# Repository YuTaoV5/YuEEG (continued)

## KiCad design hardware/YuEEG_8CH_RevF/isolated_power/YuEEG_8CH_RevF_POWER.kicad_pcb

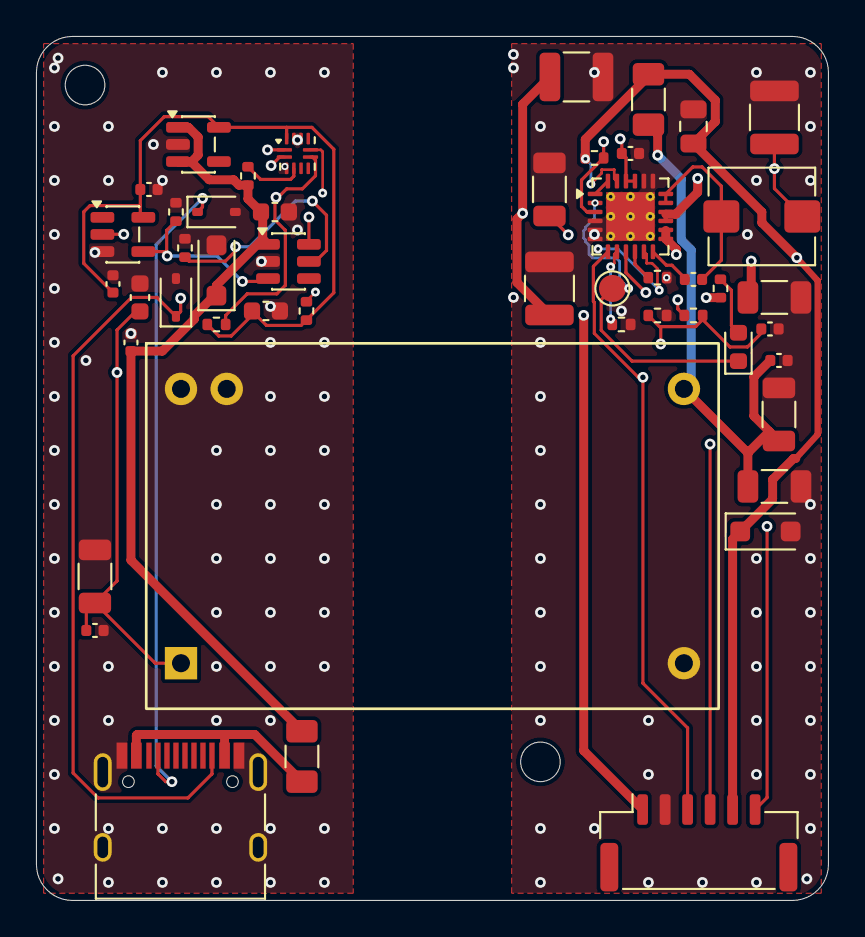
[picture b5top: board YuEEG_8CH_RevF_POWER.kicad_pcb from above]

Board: 4 copper layers, 44.0 x 48.0 mm, 50 parts (0 on the bottom side), 29 nets.

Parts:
C601: 4.7u 16V X7R; C_0805_2012Metric
C602, C605, C606: 47u 16V X7R; C_1210_3225Metric
C603, C609, C706, C707, C709, C1202, C1204: 100n 16V; C_0402_1005Metric
C604: 22u 16V X7R; C_1206_3216Metric
C607: 22u 25V X7R; C_1206_3216Metric
C608: 47n 25V X7R; C_0402_1005Metric
C704: 1u 16V; C_0603_1608Metric
C705: 1u 10V; C_0603_1608Metric
C708: 4.7u 16V; C_0603_1608Metric
C710, C1201, C1203: 10u 25V X7R; C_1206_3216Metric
D601, D701: SMF5.0A; D_SOD-123F
D902, D903: PESD5V0S1BA; D_SOD-323
F602: 1A hold PTC; Fuse_1206_3216Metric
F701: 1.5A hold PTC; Fuse_1206_3216Metric
H1205, H1206: M2 INSULATED MOUNT; MountingHole_2.2mm_M2
J901: USB-C CHARGE / POWER - NO DATA; USB_C_Receptacle_HRO_TYPE-C-31-M-12
J1204: TO MAIN J1202 / GH6; JST_GH_SM06B-GHS-TB_1x06-1MP_P1.25mm_Horizontal
L601: 1uH SRP5030T-1R0M / Isat11A; L_Bourns_SRP5030T
LED601: CHARGING; LED_0603_1608Metric
R601, R602: 10k 1%; R_0402_1005Metric
R603: 1.50k 1%; R_0402_1005Metric
R604: 1.14k 1%; R_0402_1005Metric
R605: 9.31k 0.1%; R_0402_1005Metric
R606: 365k 0.1%; R_0402_1005Metric
R609: 2.2k; R_0402_1005Metric
R705: 887k 1%; R_0402_1005Metric
R706: 23.7k 1%; R_0402_1005Metric
R707: 100k; R_0402_1005Metric
R1205: 1M CE DEFAULT OFF; R_0402_1005Metric
TP606: CHG_STAT; TestPoint_Pad_D1.5mm
U601: BQ25886RGER; Texas_RGE0024H_VQFN-24-1EP_4x4mm_P0.5mm_EP2.7x2.7mm_Thermal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
U702: TLV75533PDBVR HOST ONLY; SOT-23-5
U703: TUSB320LAIRWBR / UFP GPIO; Texas_X2QFN-12_1.6x1.6mm_P0.4mm
U704: SN74LVC1G04DBVR; SOT-23-5
U705: TPS2553DBVR; SOT-23-6
U706: THM 6-0511 / STANDARD PINOUT; THM6_Standard

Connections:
CC_HIGH_N: R601.2, U703.7, U704.2
CC_MODE2: R602.2, U703.8
CC_VBUS_DET: R705.2, U703.4
CHARGE_CC1: D902.1, J901.A5, U703.1
CHARGE_CC2: D903.1, J901.B5, U703.2
CHARGE_HOST_3V3: C705.1, C706.1, C707.1, R601.1, R602.1, U702.5, U703.12, U704.5
CHARGE_HOST_5V: C704.1, C709.1, D701.1, F701.2, R705.1, U702.1, U702.3, U705.1
CHARGE_HOST_DCDC_IN: C708.1, C1201.1, C1202.1, U705.6, U706.1
CHARGE_HOST_GND: C704.2, C705.2, C706.2, C707.2, C708.2, C709.2, C1201.2, C1202.2, D701.2, D902.2, D903.2, J901.A1, J901.A12, J901.B1, J901.B12, J901.S1, R706.2, R707.2, U702.2, U703.3, U703.10, U703.11, U704.3, U705.2, U706.23, U706.24
CHARGE_HOST_ILIM: R706.1, U705.5
CHARGE_HOST_POWER_EN: R707.1, U704.4, U705.3
CHARGE_HOST_RAW: F701.1, J901.A4, J901.A9, J901.B4, J901.B9
CHG_BOOT: C608.1, U601.12
CHG_CE: J1204.4, R1205.2, U601.3
CHG_DETECT: U601.1, U601.24
CHG_ILIM: R603.1, U601.8
CHG_ISET: R604.1, U601.10
CHG_PG: J1204.6, U601.9
CHG_PMID: C602.1, C603.1, L601.1, U601.21, U601.22
CHG_REGN: C604.1, R605.1, U601.11
CHG_STAT: LED601.1, TP606.1, U601.2
CHG_SW: C608.2, L601.2, U601.17, U601.18
CHG_SYS: C605.1, C606.1, U601.15, U601.16
CHG_TS: C609.1, J1204.3, R605.2, R606.1, U601.7
GND: C601.2, C602.2, C603.2, C604.2, C605.2, C606.2, C607.2, C609.2, C710.2, C1203.2, C1204.2, D601.2, J1204.2, R603.2, R604.2, R606.2, U601.4, U601.5, U601.6, U601.19, U601.20, U601.25, U706.12
LED_CHG_A: LED601.2, R609.2
PACK_POS: C607.1, J1204.1, U601.13, U601.14
USB5: C601.1, D601.1, F602.2, J1204.5, R609.1, R1205.1, U601.23
USB_RAW: C710.1, C1203.1, C1204.1, F602.1, U706.13

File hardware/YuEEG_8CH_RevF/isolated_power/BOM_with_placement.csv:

Reference,Value,Footprint,Side,X_mm_from_left,Y_mm_from_top,Rotation_deg
C1201,10u 25V X7R,Capacitor_SMD:C_1206_3216Metric,TOP,3.25,30.0,90.0
C1202,100n 16V,Capacitor_SMD:C_0402_1005Metric,TOP,3.25,33.0,0.0
C1203,10u 25V X7R,Capacitor_SMD:C_1206_3216Metric,TOP,41.25,21.0,90.0
C1204,100n 16V,Capacitor_SMD:C_0402_1005Metric,TOP,41.25,18.0,0.0
C601,4.7u 16V X7R,Capacitor_SMD:C_0805_2012Metric,TOP,36.5,5.0,90.0
C602,47u 16V X7R,Capacitor_SMD:C_1210_3225Metric,TOP,41.0,4.5,90.0
C603,100n 16V,Capacitor_SMD:C_0402_1005Metric,TOP,33.0,6.5,0.0
C604,22u 16V X7R,Capacitor_SMD:C_1206_3216Metric,TOP,28.5,8.5,90.0
C605,47u 16V X7R,Capacitor_SMD:C_1210_3225Metric,TOP,28.5,14.0,90.0
C606,47u 16V X7R,Capacitor_SMD:C_1210_3225Metric,TOP,30.0,2.25,0.0
C607,22u 25V X7R,Capacitor_SMD:C_1206_3216Metric,TOP,41.0,14.5,0.0
C608,47n 25V X7R,Capacitor_SMD:C_0402_1005Metric,TOP,36.5,13.5,0.0
C609,100n 16V,Capacitor_SMD:C_0402_1005Metric,TOP,40.75,16.25,0.0
C704,1u 16V,Capacitor_SMD:C_0603_1608Metric,TOP,13.25,9.75,0.0
C705,1u 10V,Capacitor_SMD:C_0603_1608Metric,TOP,12.75,15.25,0.0
C706,100n 16V,Capacitor_SMD:C_0402_1005Metric,TOP,6.25,8.5,0.0
C707,100n 16V,Capacitor_SMD:C_0402_1005Metric,TOP,4.25,13.75,90.0
C708,4.7u 16V,Capacitor_SMD:C_0603_1608Metric,TOP,5.75,14.5,90.0
C709,100n 16V,Capacitor_SMD:C_0402_1005Metric,TOP,5.25,17.0,90.0
C710,10u 25V X7R,Capacitor_SMD:C_1206_3216Metric,TOP,41.0,25.0,0.0
D601,SMF5.0A,Diode_SMD:D_SOD-123F,TOP,40.5,27.5,0.0
D701,SMF5.0A,Diode_SMD:D_SOD-123F,TOP,10.0,13.0,90.0
D902,PESD5V0S1BA,Diode_SMD:D_SOD-323,TOP,10.0,9.75,0.0
D903,PESD5V0S1BA,Diode_SMD:D_SOD-323,TOP,7.75,14.5,90.0
F602,1A hold PTC,Fuse:Fuse_1206_3216Metric,TOP,34.0,3.5,90.0
F701,1.5A hold PTC,Fuse:Fuse_1206_3216Metric,TOP,14.75,40.0,90.0
H1205,M2 INSULATED MOUNT,MountingHole:MountingHole_2.2mm_M2,TOP,2.7,2.7,0.0
H1206,M2 INSULATED MOUNT,MountingHole:MountingHole_2.2mm_M2,TOP,28.0,40.3,0.0
J1204,TO MAIN J1202 / GH6,Connector_JST:JST_GH_SM06B-GHS-TB_1x06-1MP_P1.25mm_Horizontal,TOP,36.8,44.8,0.0
J901,USB-C CHARGE / POWER - NO DATA,Connector_USB:USB_C_Receptacle_HRO_TYPE-C-31-M-12,TOP,8.0,44.0,0.0
L601,1uH SRP5030T-1R0M / Isat11A,Inductor_SMD:L_Bourns_SRP5030T,TOP,40.3,10.0,180.0
LED601,CHARGING,LED_SMD:LED_0603_1608Metric,TOP,39.0,17.25,90.0
R1205,1M CE DEFAULT OFF,Resistor_SMD:R_0402_1005Metric,TOP,31.0,6.75,0.0
R601,10k 1%,Resistor_SMD:R_0402_1005Metric,TOP,10.0,16.0,0.0
R602,10k 1%,Resistor_SMD:R_0402_1005Metric,TOP,15.0,15.25,90.0
R603,1.50k 1%,Resistor_SMD:R_0402_1005Metric,TOP,32.5,16.0,0.0
R604,1.14k 1%,Resistor_SMD:R_0402_1005Metric,TOP,34.5,13.4,0.0
R605,9.31k 0.1%,Resistor_SMD:R_0402_1005Metric,TOP,36.5,15.5,0.0
R606,365k 0.1%,Resistor_SMD:R_0402_1005Metric,TOP,34.5,15.5,0.0
R609,2.2k,Resistor_SMD:R_0402_1005Metric,TOP,38.0,14.0,90.0
R705,887k 1%,Resistor_SMD:R_0402_1005Metric,TOP,11.75,7.75,90.0
R706,23.7k 1%,Resistor_SMD:R_0402_1005Metric,TOP,8.25,11.75,90.0
R707,100k,Resistor_SMD:R_0402_1005Metric,TOP,7.75,9.75,90.0
TP606,CHG_STAT,TestPoint:TestPoint_Pad_D1.5mm,TOP,32.0,14.0,0.0
U601,BQ25886RGER,Package_DFN_QFN:Texas_RGE0024H_VQFN-24-1EP_4x4mm_P0.5mm_EP2.7x2.7mm_ThermalVias,TOP,33.0,10.0,0.0
U702,TLV75533PDBVR HOST ONLY,Package_TO_SOT_SMD:SOT-23-5,TOP,9.0,6.0,0.0
U703,TUSB320LAIRWBR / UFP GPIO,Package_DFN_QFN:Texas_X2QFN-12_1.6x1.6mm_P0.4mm,TOP,14.5,6.5,0.0
U704,SN74LVC1G04DBVR,Package_TO_SOT_SMD:SOT-23-5,TOP,4.8,11.0,0.0
U705,TPS2553DBVR,Package_TO_SOT_SMD:SOT-23-6,TOP,14.0,12.5,0.0
U706,THM 6-0511 / STANDARD PINOUT,YuEEG:THM6_Standard,TOP,22.0,27.2,0.0

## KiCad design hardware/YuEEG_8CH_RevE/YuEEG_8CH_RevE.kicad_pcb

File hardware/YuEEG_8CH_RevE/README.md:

# YuEEG Rev E 工程评审版

94 × 122 mm、四层、378 个元件、15 页原理图。以 `YuEEG_8CH_RevE.kicad_pro` 打开 KiCad 9 工程。

- 双 Type-C 同边：DATA/FLASH 为隔离原生 USB，CHARGE/POWER 为独立充电/供电；VBUS 不并联。
- ESP32-S3-WROOM-1-N16R8；USB CDC 与 Wi-Fi UDP 并行；SDMMC microSD 备份。
- DWO DO0200PFS12 RM67162 1.91 英寸 AMOLED，专用 2.8/1.8 V 电源及电平转换；需要确认供应商版本和配套排线。
- 0.53 mm Panasonic EVPBB2A9B000 超薄贴片 RESET/BOOT/REC；电解电容和按钮均在正面。
- CH1–8、REF、BIAS 同列；移除外置模拟前端扩展接口，恢复直接对称 P/N 输入路径。
- 圆角板框、圆角丝印分区、分组状态灯；黑色阻焊/白字/ENIG 外观。

## 文件入口

- [原理图 PDF](YuEEG_8CH_RevE.pdf)
- [设计分析与一手资料](REV_E_REVIEW.md)
- [静态检查结果](review/PCB_validation.json)
- [加工/装配要求](fabrication_review/ASSEMBLY_NOTES.md)
- [模块、排线和支撑件清单](ASSEMBLY_EXTRAS.csv)
- [固件操作说明](firmware/ads1299_driver/README.md)
- [正面预览](review/PCB_3D_top.png) · [背面预览](review/PCB_3D_bottom.png)

原理图、PCB、加工文件、引脚复核及固件快照由 CHECKSUMS.json 绑定。过孔填孔/铜封帽、模块与外壳的实际配合、屏幕初始化、SD 卡延迟、并行传输及模拟噪声需要首板验证。3D 中屏幕图案仅为布局示意，模型不替代供应商机械图。工程评审通过不等于人体使用放行或医疗认证。

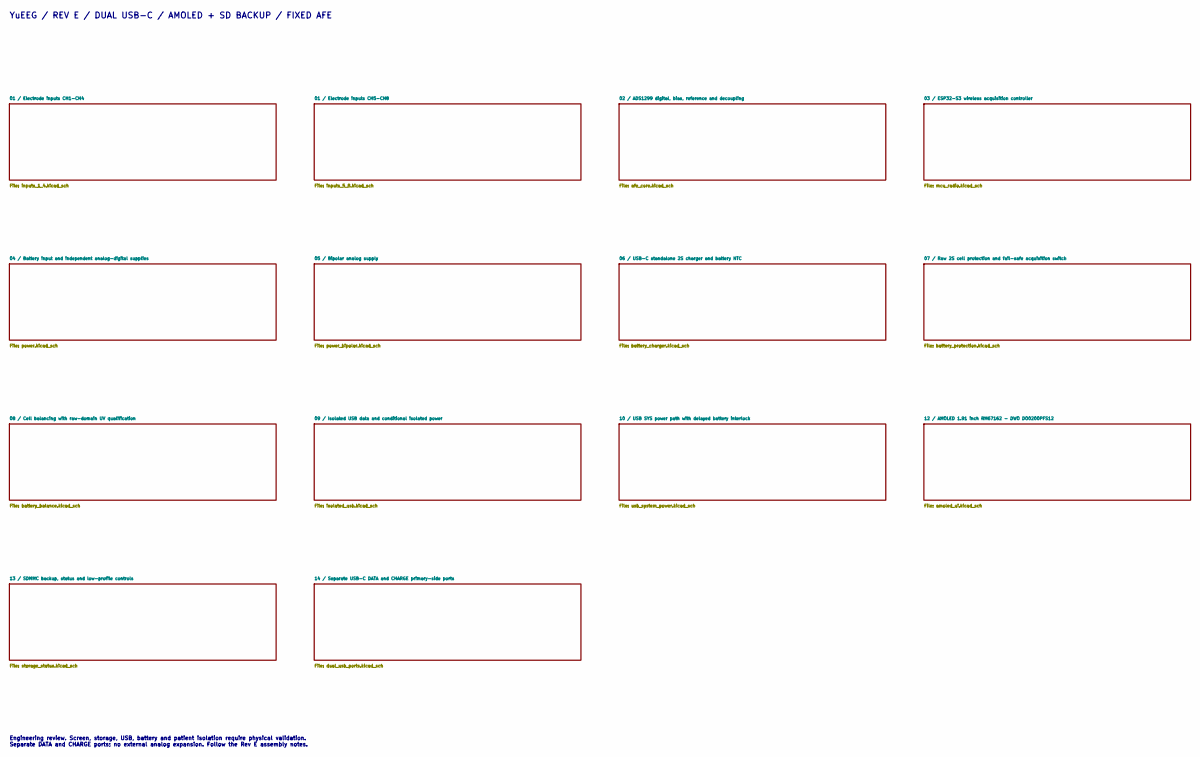
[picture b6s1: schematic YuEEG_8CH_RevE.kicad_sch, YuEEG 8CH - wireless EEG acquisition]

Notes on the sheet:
YuEEG / REV E / DUAL USB-C / AMOLED + SD BACKUP / FIXED AFE
Engineering review. Screen, storage, USB, battery and patient isolation require physical validation. Separate DATA and CHARGE ports; no external analog expansion. Follow the Rev E assembly notes.

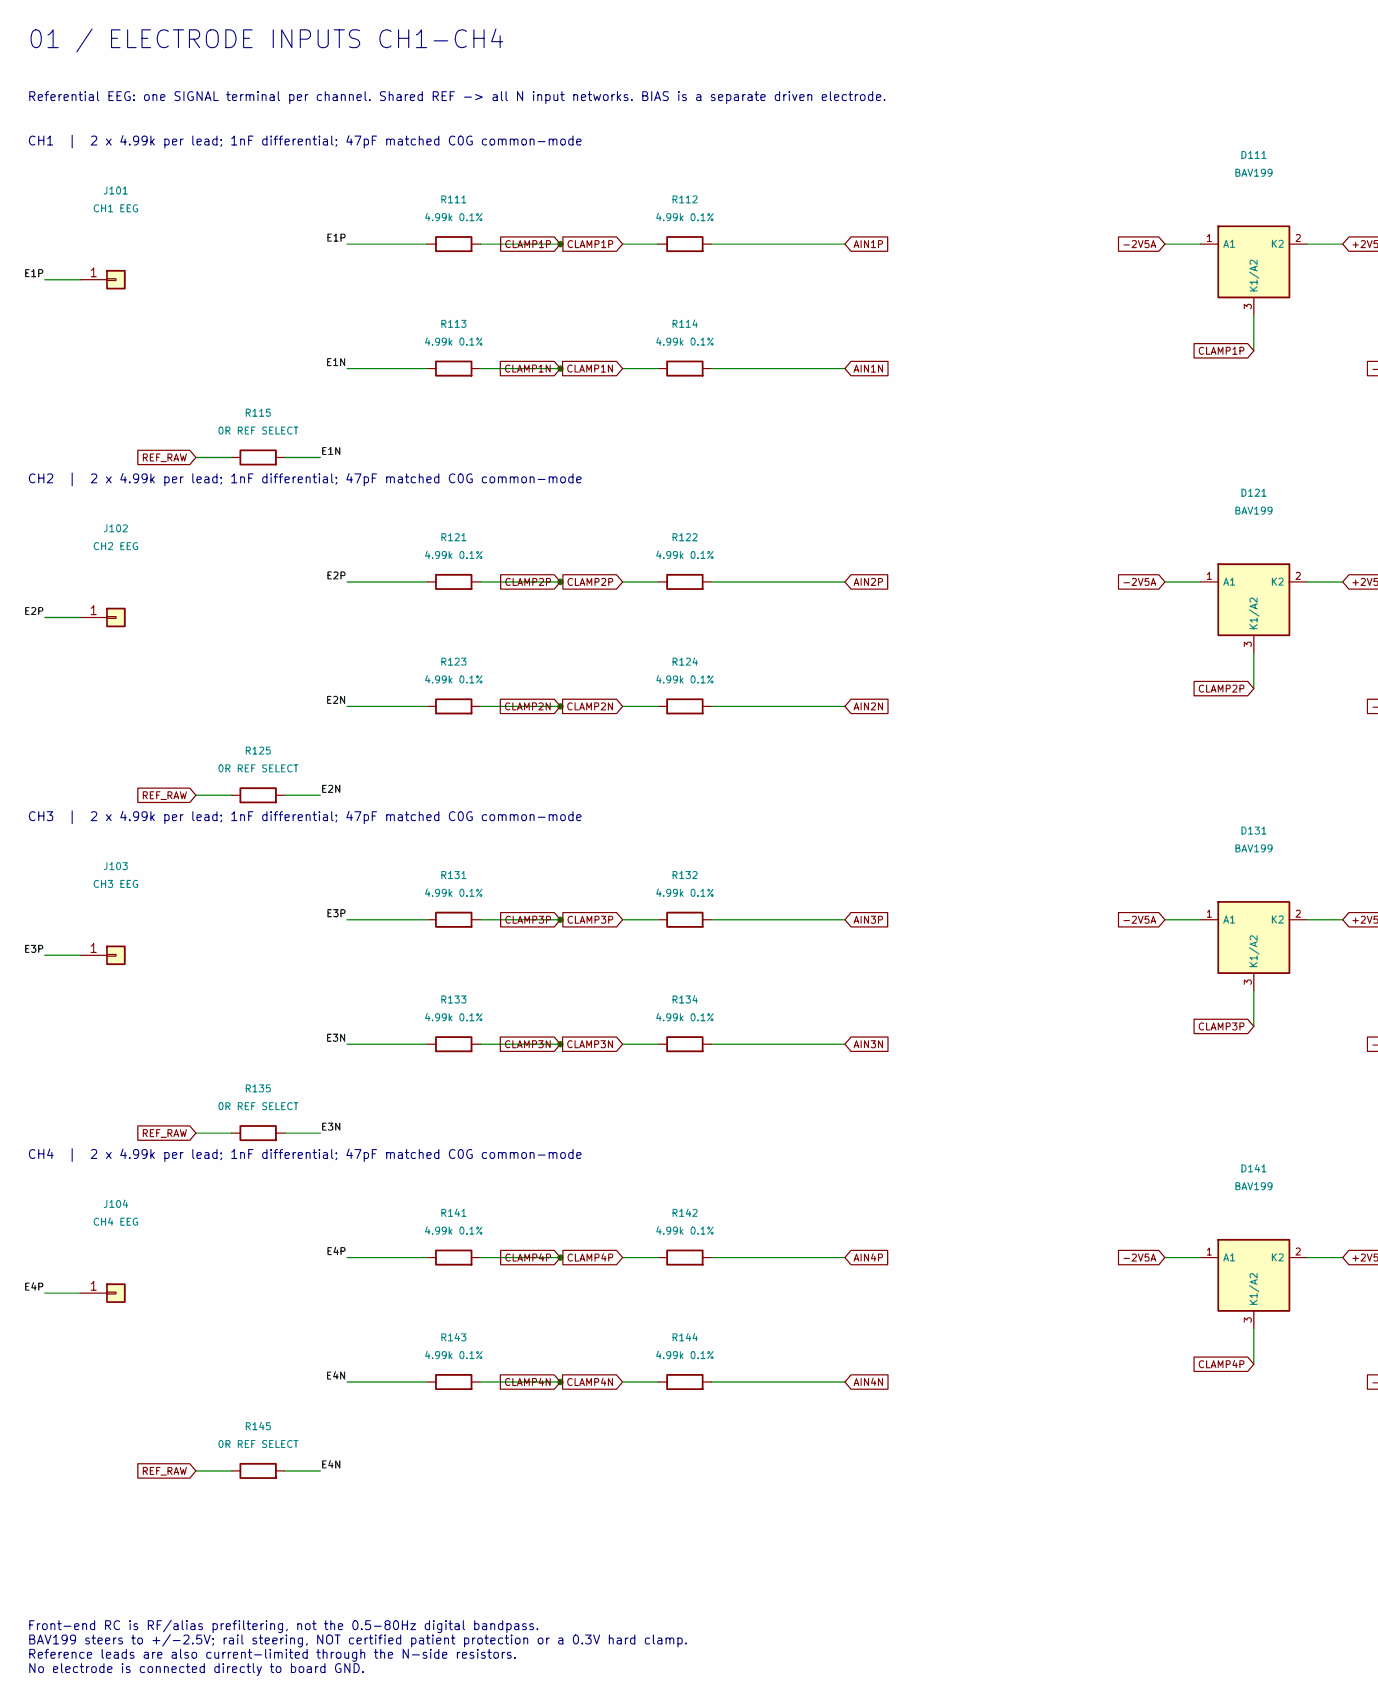
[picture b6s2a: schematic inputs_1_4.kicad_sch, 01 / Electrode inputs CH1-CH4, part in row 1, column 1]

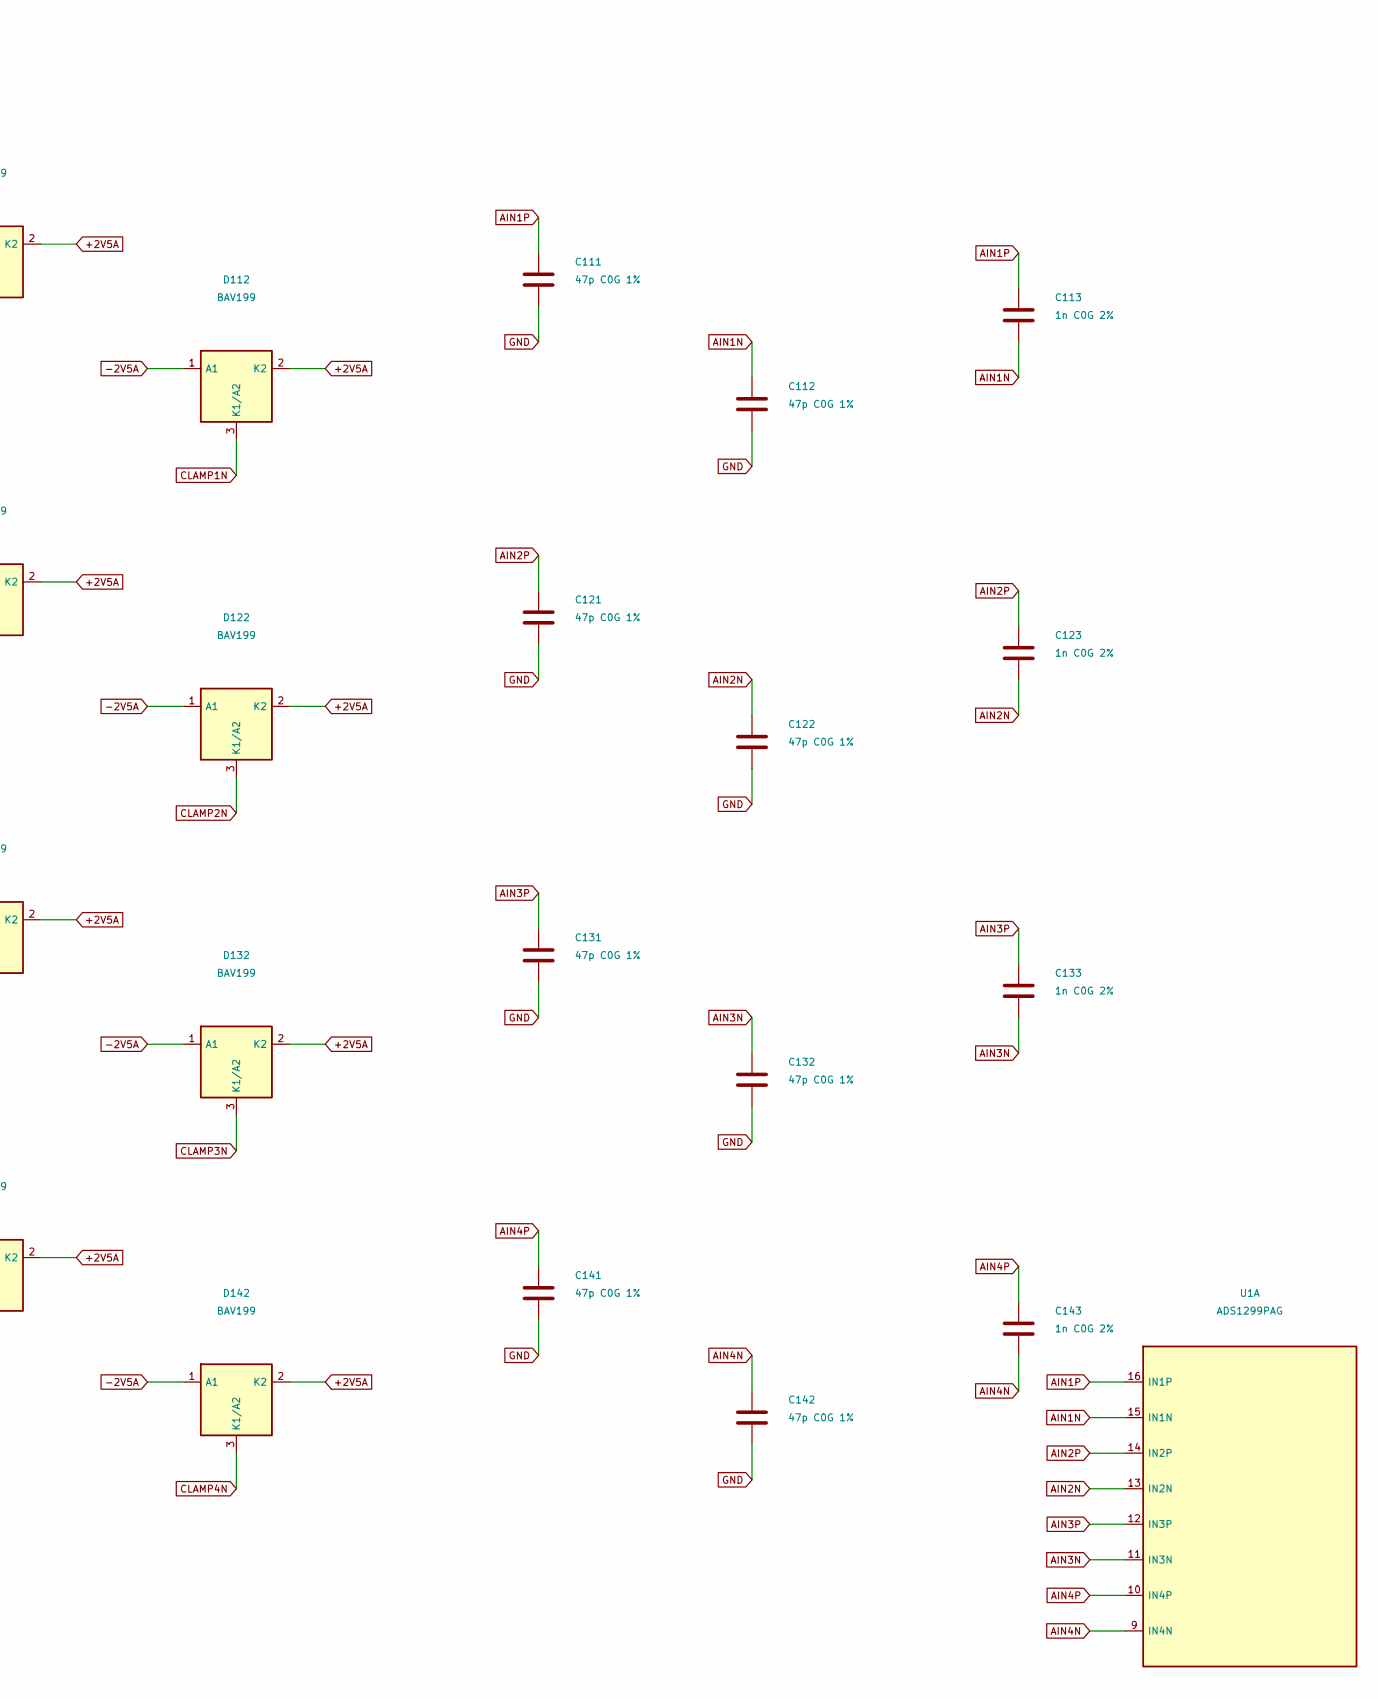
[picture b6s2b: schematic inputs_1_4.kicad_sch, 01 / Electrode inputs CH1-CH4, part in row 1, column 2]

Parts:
C111, C112, C121, C122, C131, C132, C141, C142: 47p C0G 1%; C_0603_1608Metric
C113, C123, C133, C143: 1n C0G 2%; C_0603_1608Metric
D111, D112, D121, D122, D131, D132, D141, D142: BAV199; SOT-23
J101: CH1 EEG; PinHeader_1x01_P2.54mm_Vertical
J102: CH2 EEG; PinHeader_1x01_P2.54mm_Vertical
J103: CH3 EEG; PinHeader_1x01_P2.54mm_Vertical
J104: CH4 EEG; PinHeader_1x01_P2.54mm_Vertical
R111, R112, R113, R114, R121, R122, R123, R124, R131, R132, R133, R134, R141, R142, R143, R144: 4.99k 0.1%; R_0603_1608Metric
R115, R125, R135, R145: 0R REF SELECT; R_0603_1608Metric
U1: ADS1299PAG; TQFP-64_10x10mm_P0.5mm

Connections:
+2V5A: D111.2 (K2), D112.2 (K2), D121.2 (K2), D122.2 (K2), D131.2 (K2), D132.2 (K2), D141.2 (K2), D142.2 (K2); also elsewhere on the board
-2V5A: D111.1 (A1), D112.1 (A1), D121.1 (A1), D122.1 (A1), D131.1 (A1), D132.1 (A1), D141.1 (A1), D142.1 (A1); also elsewhere on the board
/01 / Electrode inputs CH1-CH4/E1N: R113.1, R115.2
/01 / Electrode inputs CH1-CH4/E1P: J101.1, R111.1
/01 / Electrode inputs CH1-CH4/E2N: R123.1, R125.2
/01 / Electrode inputs CH1-CH4/E2P: J102.1, R121.1
/01 / Electrode inputs CH1-CH4/E3N: R133.1, R135.2
/01 / Electrode inputs CH1-CH4/E3P: J103.1, R131.1
/01 / Electrode inputs CH1-CH4/E4N: R143.1, R145.2
/01 / Electrode inputs CH1-CH4/E4P: J104.1, R141.1
AIN1N: C112.1, C113.2, R114.2, U1.15 (IN1N)
AIN1P: C111.1, C113.1, R112.2, U1.16 (IN1P)
AIN2N: C122.1, C123.2, R124.2, U1.13 (IN2N)
AIN2P: C121.1, C123.1, R122.2, U1.14 (IN2P)
AIN3N: C132.1, C133.2, R134.2, U1.11 (IN3N)
AIN3P: C131.1, C133.1, R132.2, U1.12 (IN3P)
AIN4N: C142.1, C143.2, R144.2, U1.9 (IN4N)
AIN4P: C141.1, C143.1, R142.2, U1.10 (IN4P)
CLAMP1N: D112.3 (K1/A2), R113.2, R114.1
CLAMP1P: D111.3 (K1/A2), R111.2, R112.1
CLAMP2N: D122.3 (K1/A2), R123.2, R124.1
CLAMP2P: D121.3 (K1/A2), R121.2, R122.1
CLAMP3N: D132.3 (K1/A2), R133.2, R134.1
CLAMP3P: D131.3 (K1/A2), R131.2, R132.1
CLAMP4N: D142.3 (K1/A2), R143.2, R144.1
CLAMP4P: D141.3 (K1/A2), R141.2, R142.1
GND: C111.2, C112.2, C121.2, C122.2, C131.2, C132.2, C141.2, C142.2; also elsewhere on the board
REF_RAW: R115.1, R125.1, R135.1, R145.1; also elsewhere on the board

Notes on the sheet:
01 / ELECTRODE INPUTS CH1-CH4
Referential EEG: one SIGNAL terminal per channel. Shared REF -> all N input networks. BIAS is a separate driven electrode.
CH1 | 2 x 4.99k per lead; 1nF differential; 47pF matched C0G common-mode
CH2 | 2 x 4.99k per lead; 1nF differential; 47pF matched C0G common-mode
CH3 | 2 x 4.99k per lead; 1nF differential; 47pF matched C0G common-mode
CH4 | 2 x 4.99k per lead; 1nF differential; 47pF matched C0G common-mode
Front-end RC is RF/alias prefiltering, not the 0.5-80Hz digital bandpass. BAV199 steers to +/-2.5V; rail steering, NOT certified patient protection or a 0.3V hard clamp. Reference leads are also current-limited through the N-side resistors. No electrode is connected directly to board GND.

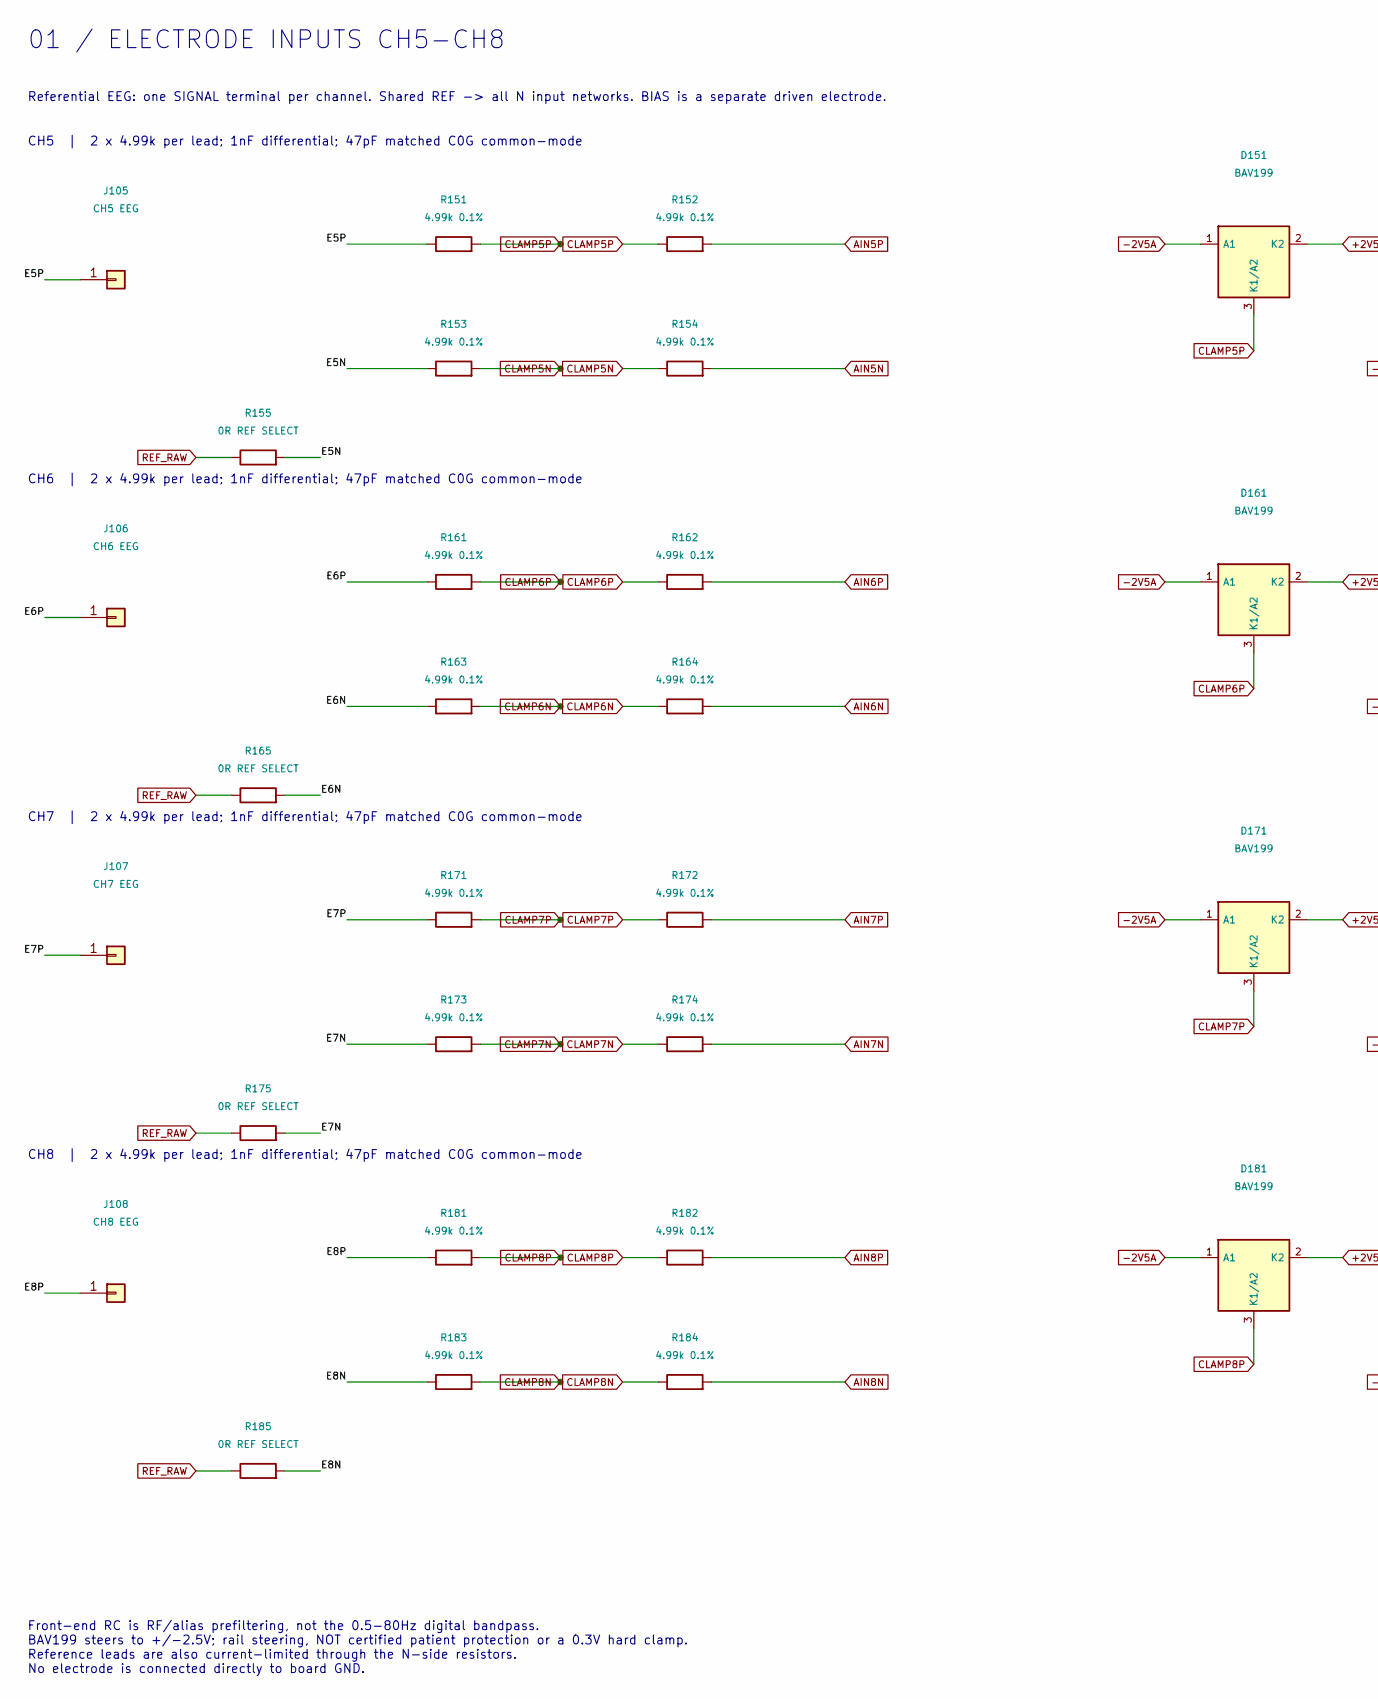
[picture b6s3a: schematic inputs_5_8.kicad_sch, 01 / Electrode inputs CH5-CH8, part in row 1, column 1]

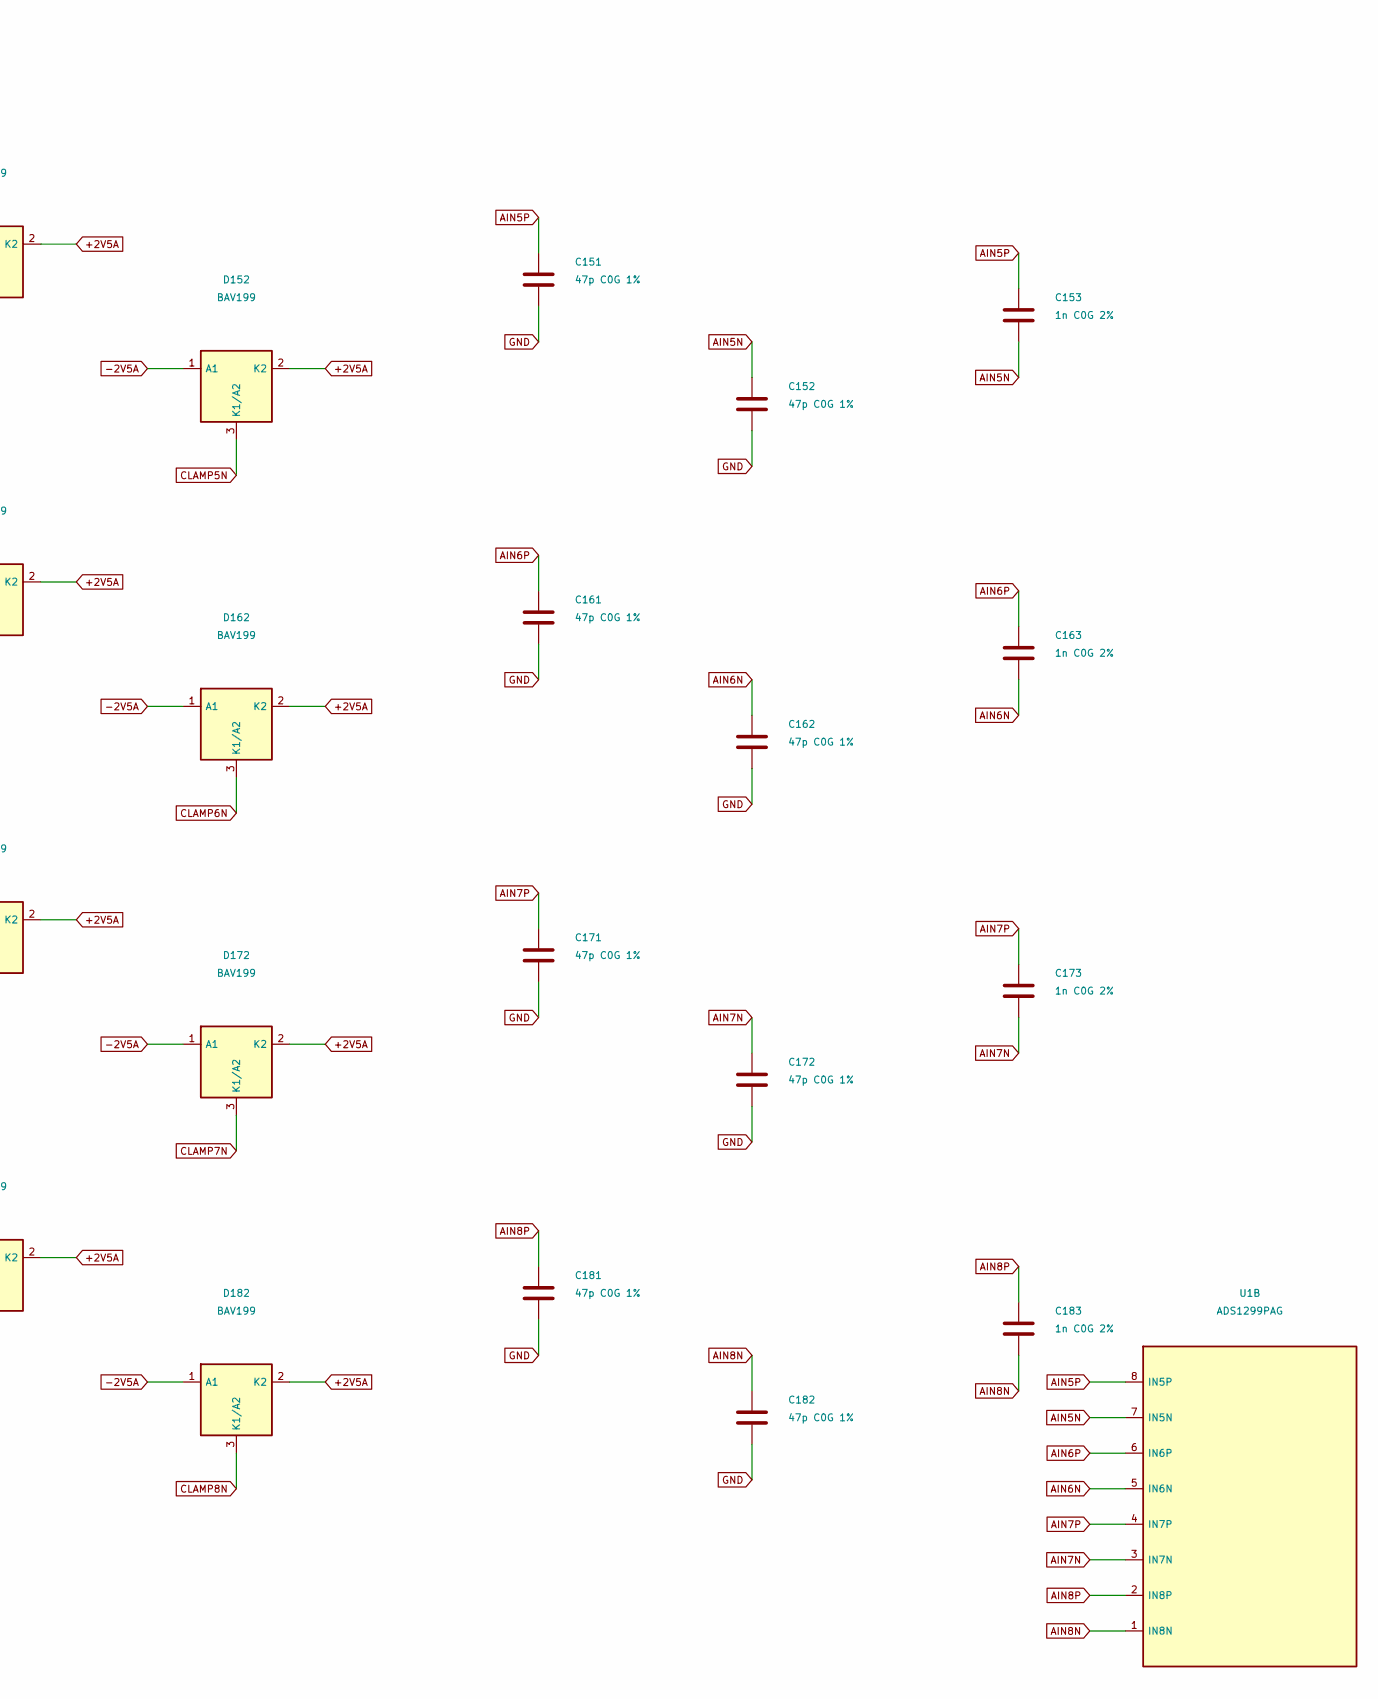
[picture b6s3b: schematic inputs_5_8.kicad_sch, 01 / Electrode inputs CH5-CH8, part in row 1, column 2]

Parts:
C151, C152, C161, C162, C171, C172, C181, C182: 47p C0G 1%; C_0603_1608Metric
C153, C163, C173, C183: 1n C0G 2%; C_0603_1608Metric
D151, D152, D161, D162, D171, D172, D181, D182: BAV199; SOT-23
J105: CH5 EEG; PinHeader_1x01_P2.54mm_Vertical
J106: CH6 EEG; PinHeader_1x01_P2.54mm_Vertical
J107: CH7 EEG; PinHeader_1x01_P2.54mm_Vertical
J108: CH8 EEG; PinHeader_1x01_P2.54mm_Vertical
R151, R152, R153, R154, R161, R162, R163, R164, R171, R172, R173, R174, R181, R182, R183, R184: 4.99k 0.1%; R_0603_1608Metric
R155, R165, R175, R185: 0R REF SELECT; R_0603_1608Metric
U1: ADS1299PAG; TQFP-64_10x10mm_P0.5mm

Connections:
+2V5A: D151.2 (K2), D152.2 (K2), D161.2 (K2), D162.2 (K2), D171.2 (K2), D172.2 (K2), D181.2 (K2), D182.2 (K2); also elsewhere on the board
-2V5A: D151.1 (A1), D152.1 (A1), D161.1 (A1), D162.1 (A1), D171.1 (A1), D172.1 (A1), D181.1 (A1), D182.1 (A1); also elsewhere on the board
/01 / Electrode inputs CH5-CH8/E5N: R153.1, R155.2
/01 / Electrode inputs CH5-CH8/E5P: J105.1, R151.1
/01 / Electrode inputs CH5-CH8/E6N: R163.1, R165.2
/01 / Electrode inputs CH5-CH8/E6P: J106.1, R161.1
/01 / Electrode inputs CH5-CH8/E7N: R173.1, R175.2
/01 / Electrode inputs CH5-CH8/E7P: J107.1, R171.1
/01 / Electrode inputs CH5-CH8/E8N: R183.1, R185.2
/01 / Electrode inputs CH5-CH8/E8P: J108.1, R181.1
AIN5N: C152.1, C153.2, R154.2, U1.7 (IN5N)
AIN5P: C151.1, C153.1, R152.2, U1.8 (IN5P)
AIN6N: C162.1, C163.2, R164.2, U1.5 (IN6N)
AIN6P: C161.1, C163.1, R162.2, U1.6 (IN6P)
AIN7N: C172.1, C173.2, R174.2, U1.3 (IN7N)
AIN7P: C171.1, C173.1, R172.2, U1.4 (IN7P)
AIN8N: C182.1, C183.2, R184.2, U1.1 (IN8N)
AIN8P: C181.1, C183.1, R182.2, U1.2 (IN8P)
CLAMP5N: D152.3 (K1/A2), R153.2, R154.1
CLAMP5P: D151.3 (K1/A2), R151.2, R152.1
CLAMP6N: D162.3 (K1/A2), R163.2, R164.1
CLAMP6P: D161.3 (K1/A2), R161.2, R162.1
CLAMP7N: D172.3 (K1/A2), R173.2, R174.1
CLAMP7P: D171.3 (K1/A2), R171.2, R172.1
CLAMP8N: D182.3 (K1/A2), R183.2, R184.1
CLAMP8P: D181.3 (K1/A2), R181.2, R182.1
GND: C151.2, C152.2, C161.2, C162.2, C171.2, C172.2, C181.2, C182.2; also elsewhere on the board
REF_RAW: R155.1, R165.1, R175.1, R185.1; also elsewhere on the board

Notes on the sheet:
01 / ELECTRODE INPUTS CH5-CH8
Referential EEG: one SIGNAL terminal per channel. Shared REF -> all N input networks. BIAS is a separate driven electrode.
CH5 | 2 x 4.99k per lead; 1nF differential; 47pF matched C0G common-mode
CH6 | 2 x 4.99k per lead; 1nF differential; 47pF matched C0G common-mode
CH7 | 2 x 4.99k per lead; 1nF differential; 47pF matched C0G common-mode
CH8 | 2 x 4.99k per lead; 1nF differential; 47pF matched C0G common-mode
Front-end RC is RF/alias prefiltering, not the 0.5-80Hz digital bandpass. BAV199 steers to +/-2.5V; rail steering, NOT certified patient protection or a 0.3V hard clamp. Reference leads are also current-limited through the N-side resistors. No electrode is connected directly to board GND.
